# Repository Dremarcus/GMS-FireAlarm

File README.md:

# GSM-FireAlarm
Požární hlásič s odesíláním zpráv přes GSM
Použitý modul Arduino nano,NiceRF, SIM800L a Digispark
Funkce:
Čidlo kouře pošle přes NiceRF a Digispark kód ->
NiceRF příjme zprávu, kterou předá Arduino NANO ->
NANO vyhodnotí zprávu a počká až bude souhlasit počet přijatých zpráv ->
Po dosažení počtu, zapne LED a spustí sirénu ->
Následně osloví SIM800L aby poslalo SMS na tel.čísla a poté zavolal na tel.čísla ->
Poté se restartuje celé zařízení.

Dlouho jsem se pokoušel zprovoznit vícenásobné poslání SMS a Volání.
Nakonec používám před každým odesláním SMS aktivaci TEXT módu a funguje to i na xy čísel pod sebou
S voláním jsem nepochopil, proč nelze opakovat volání...
Až po nějaké době(cca2 měsíce sem tam odpoledne) jsem zkusil restartovat modul SIM800L a ejhle, ono to jede...
Takže po zavolání - reset - a před dalším voláním - start -

Použil jsem NANO ale má to nevýhodu s pamětí.
Omezení pro proměnné je jen 1kB, nevím jesti větší modul má více...
Tudíž je omezení na 2 telefonní čísla
Chtěl jsem dát 7 ale 190 bytů se mu zdá málo

Celkový program zabírá:
Projekt zabírá 9220 bytů (64%)  úložného místa pro program. Maximum je 14336 bytů.
Globální proměnné zabírají 764 bytů (74%)  dynamické paměti, 260 bytů zůstává pro lokální proměnné. Maximum je 1024 bytů.

Použitá knihovna GSMSim.h je naprosto perfektní!!! Díky erdemarslan

Přikládám Eagle DPS celého projektu
DPS je vyrobena pro krabici DLS routeru Zyxel P-660HN-T3A
Ve schématu je jen chybička- R6 je výstup na sirénu (bez odporu)

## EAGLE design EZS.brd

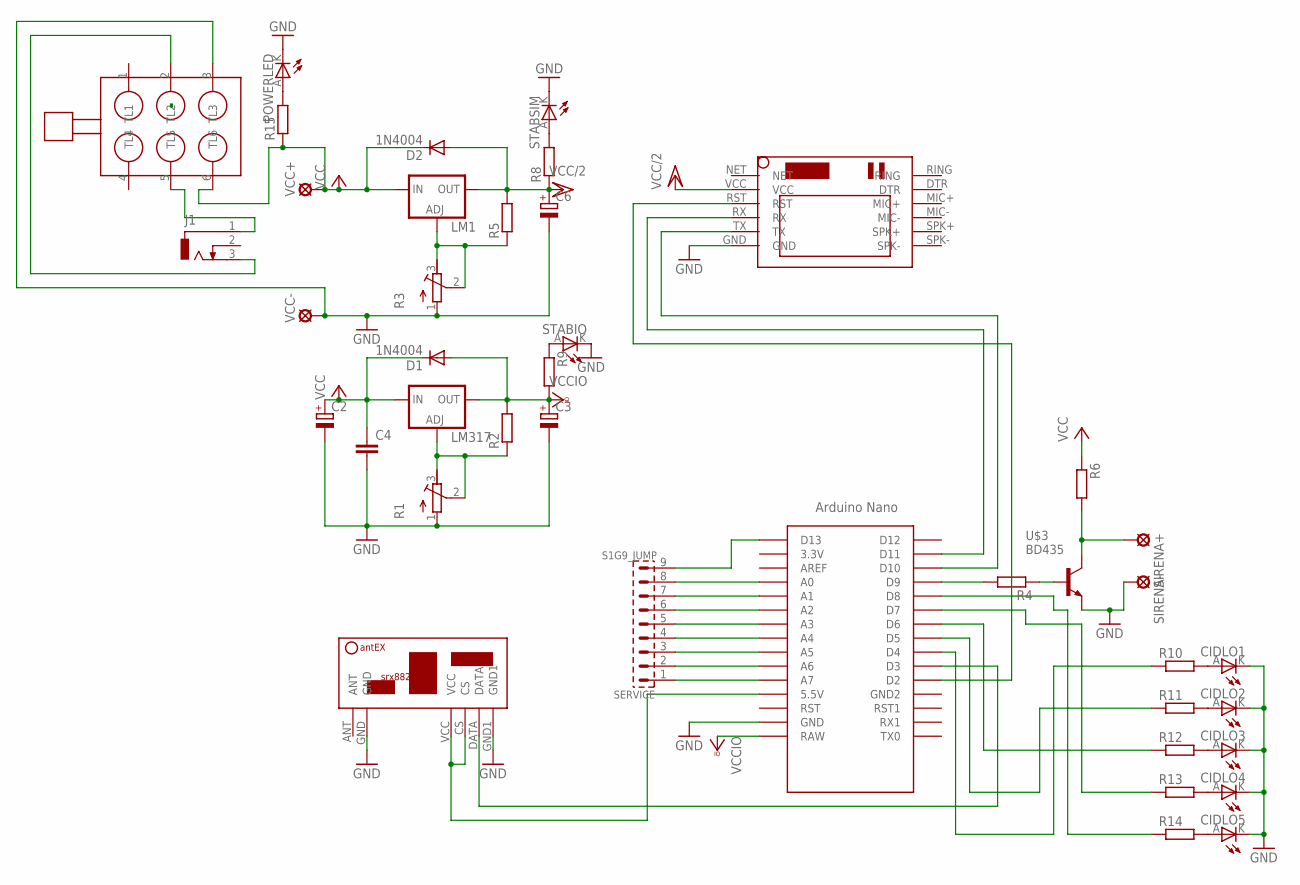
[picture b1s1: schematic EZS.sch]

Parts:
C2, C3, C6: CPOL-EUE3.5-8; E3,5-8
C4: C-EU102-064X133; C102-064X133
CIDLO1, CIDLO2, CIDLO3, CIDLO4, CIDLO5: LEDLED3MM; LED3MM
D1, D2: 1N4004; DO41-10
J1: DCJ0303
LM1, LM317: LM317TS; 317TS
POWERLED: LEDLED3MM; LED3MM
R1, R3: R-TRIMM64Y; RTRIM64Y
R2, R4, R5, R6, R8, R9, R10, R11, R12, R13, R14, R15: R-EU_0207/10; 0207/10
SERVICE: S1G9_JUMP; S1G9_JUM
SIM800L: SIM800LMODULE
SIRENA+: LSP11
SIRENA-: LSP11
STABIO: LEDLED3MM; LED3MM
STABSIM: LEDLED3MM; LED3MM
U$1: NANO
U$2: RSX882; SRX882
U$3: BD435
U$4: TLACITKO
VCC+: LSP11
VCC-: LSP11

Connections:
GND: C2.-, C3.-, C4.2, C6.-, CIDLO1.K (C), CIDLO2.K (C), CIDLO3.K (C), CIDLO4.K (C), CIDLO5.K (C), POWERLED.K (C), R1.1 (A), R3.1 (A), SIM800L.GND, SIRENA-.MP, STABIO.K (C), STABSIM.K (C), U$1.GND, U$2.GND, U$2.GND1, U$3.E, U$4.3 (TL3), VCC-.MP
unnamed: U$1.D3, U$2.DATA
unnamed: LM317.1 (ADJ), R1.2 (S), R1.3 (E), R2.1
unnamed: U$1.5V (5.5V), U$2.CS, U$2.VCC
unnamed: R8.2, STABSIM.A
unnamed: SIM800L.RX, U$1.D11
unnamed: LM1.1 (ADJ), R3.2 (S), R3.3 (E), R5.1
unnamed: SIM800L.TX, U$1.D10
unnamed: R4.2, U$1.D9
unnamed: R4.1, U$3.B
unnamed: R6.2, SIRENA+.MP, U$3.C
unnamed: J1.1, U$4.5 (TL5)
unnamed: J1.3, U$4.2 (TL2)
unnamed: POWERLED.A, R15.2
unnamed: SIM800L.RST, U$1.D2
unnamed: CIDLO1.A, R10.2
unnamed: CIDLO2.A, R11.2
unnamed: CIDLO3.A, R12.2
unnamed: CIDLO4.A, R13.2
unnamed: CIDLO5.A, R14.2
unnamed: R13.1, U$1.D7
unnamed: R10.1, U$1.D4
unnamed: R12.1, U$1.D6
unnamed: SERVICE.1, U$1.A7
unnamed: R9.1, STABIO.A
unnamed: R11.1, U$1.D5
unnamed: R14.1, U$1.D8
unnamed: SERVICE.2, U$1.A6
unnamed: SERVICE.3, U$1.A5
unnamed: SERVICE.4, U$1.A4
unnamed: SERVICE.5, U$1.A3
unnamed: SERVICE.6, U$1.A2
unnamed: SERVICE.7, U$1.A1
unnamed: SERVICE.8, U$1.A0
unnamed: SERVICE.9, U$1.D13
VCC: C2.+, C4.1, D1.C, D2.C, LM1.3 (IN), LM317.3 (IN), R6.1, R15.1, U$4.6 (TL6), VCC+.MP
VCC/2: C6.+, D2.A, LM1.2 (OUT), R5.2, R8.1, SIM800L.VCC
VCCIO: C3.+, D1.A, LM317.2 (OUT), R2.2, R9.2, U$1.RAW

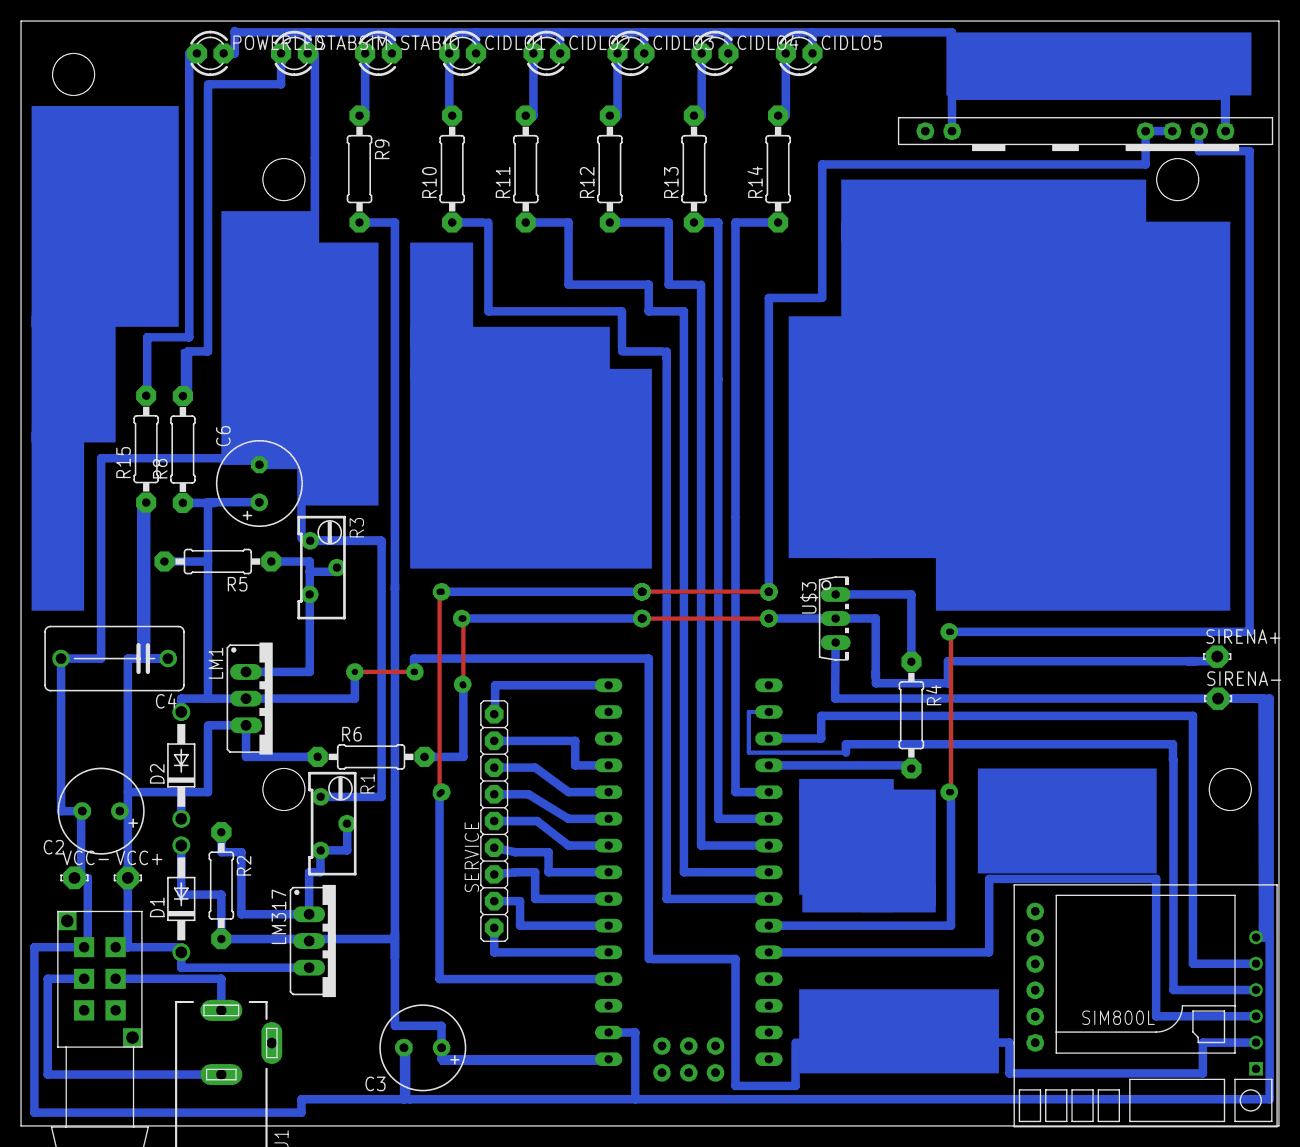
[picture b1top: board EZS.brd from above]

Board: 2 copper layers, 119.6 x 105.1 mm, 41 parts (0 on the bottom side), 38 nets.

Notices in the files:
parts and their libraries:
Copyright (C) Vlada 2004-2005
Copyright (C) PaJa 2011-2014
